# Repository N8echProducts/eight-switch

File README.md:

# eight-switch
Open Source Utf-8 direct keyboard

## Buying
- [n8ech store](https://store.n8ech.com/collections/eight-switch-binary-keyboard)
- [Tindie (KB Edition DIY Kit)](https://www.tindie.com/products/n8ech/eight-switch-kb-edition-diy-kit/)

## Using
ASCII inputs work on more-or-less any device that takes a usb keyboard out of the box.
1. Plug in the eight-switch
1. Select a printable ascii code using the toggle switches
1. Press the button

## UTF-8
Utf-8 inputs are currently supported on the following systems, but some only after enabling unicode direct hex input on the computer.

### MacOS
1. Enable unicode direct input (only needed once)
    1. Open "System Settings"
    2. Open the "Keyboard" menu
    3. Open the "Input Sources" menu
    4. Add "Unicode Hex Input" from the "Others" menu
2. Flip all keys on your eight-switch off
3. Plug in the eight-switch

### Windows
1. Enable Unicode direct input (only needed once)
    1. Press Win + R to open "RUN"
    2. Type regedit and hit Enter to open the Registry Editor.
    3. Navigate to HKEY_CURRENT_USER\Control Panel\Input Method.
    4. Right-click the empty space in the right pane,
    5. select New > String Value, and name it EnableHexNumpad.Double-click EnableHexNumpad,
    6. set the Value data to 1,
    7. click OK.
    8. Restart your computer
1. Flip all keys on your eight-switch off except for the right-most switch (00000001)
2. Plug in the eight-switch

## Firmware Updates
Firmware can be found on the ["Releases" page](https://github.com/N8echProducts/eight-switch/releases) in this repository
### Flashing new updates
the eight-switch is based on the Raspberry pi rp2040 chip, which makes flashing the firmware trivial.
1. Hold down the "flash firmware" button (the button that isn't the push-button to send sequences to the computer) while plugging the device into your computer.
2. drag the .uf2 file from your computer to the drive the device is presenting itself as
3. wait for the device to restart

## QMK mode
The KB editions can be loaded with [QMK](https://qmk.fm)
- Note: The qmk implementation is not the core implementation of the project and is thus vibecoded. Anything in the `qmk-firmware` directory may be considered "slop" but it does seem to work as far as I have tested it. Prebuilt `.uf2` files for a nonsense keymap are attached to releases

## AI disclosure
The product and firmware was all hand-designed/coded with only chatbot style glorified Google Search patterns to/from Claude code.
The utf-8 booklet was nearly entirely vibecoded beyond the initial implementation.
The CI setup was painfully ai assisted and I regret not doing it myself due to the hassle the AI brought
All documentation is written by hand with AI used as glorified Google search.

My general policy: I strive to put out work at the highest quality, with an emphasis on the things people will care about and interact with the most. I allow AI in my workflows only in places where it would not be feasible to do it by hand, and where I can carefully monitor and guage the output to be to my standards.

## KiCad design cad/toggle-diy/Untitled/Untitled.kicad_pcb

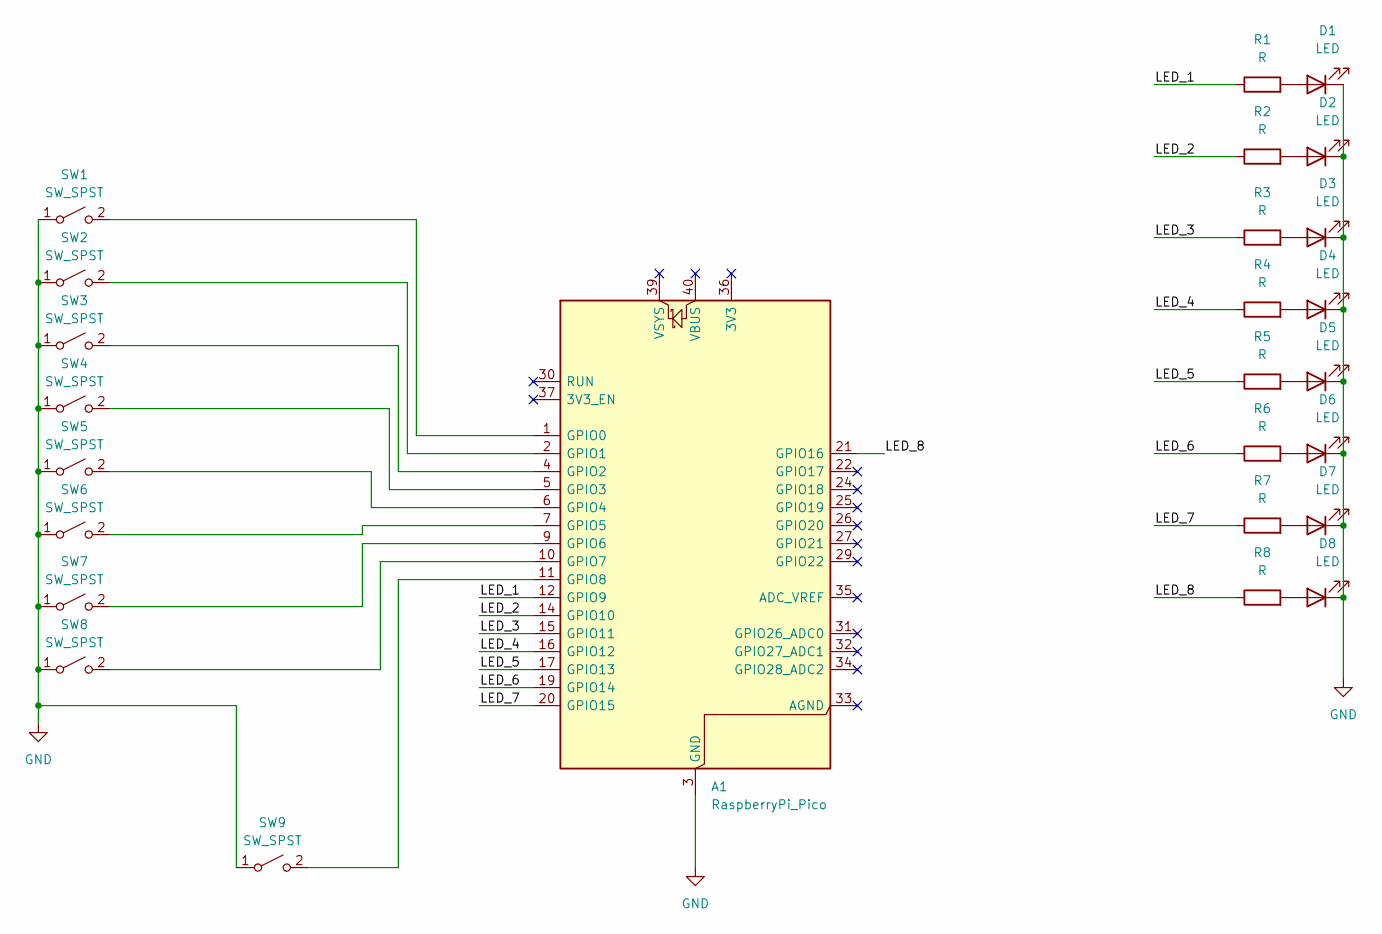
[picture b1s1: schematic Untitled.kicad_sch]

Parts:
A1: RaspberryPi_Pico; RaspberryPi_Pico_Common_SMD
D1, D2, D3, D4, D5, D6, D7, D8: LED; LED_D5.0mm
R1, R2, R3, R4, R5, R6, R7, R8: R; R_Axial_DIN0207_L6.3mm_D2.5mm_P10.16mm_Horizontal
SW1, SW2, SW3, SW4, SW5, SW6, SW7, SW8: SW_SPST; mn11ss1w03_1
SW9: SW_SPST; SW_Cherry_MX_PCB_1.00u

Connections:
/LED_1: A1.12 (GPIO9), R1.1
/LED_2: A1.14 (GPIO10), R2.1
/LED_3: A1.15 (GPIO11), R3.1
/LED_4: A1.16 (GPIO12), R4.1
/LED_5: A1.17 (GPIO13), R5.1
/LED_6: A1.19 (GPIO14), R6.1
/LED_7: A1.20 (GPIO15), R7.1
/LED_8: A1.21 (GPIO16), R8.1
GND: A1.3 (GND), A1.8 (GND), A1.13 (GND), A1.18 (GND), A1.23 (GND), A1.28 (GND), A1.38 (GND), D1.1 (K), D2.1 (K), D3.1 (K), D4.1 (K), D5.1 (K), D6.1 (K), D7.1 (K), D8.1 (K), SW1.1 (A), SW2.1 (A), SW3.1 (A), SW4.1 (A), SW5.1 (A), SW6.1 (A), SW7.1 (A), SW8.1 (A), SW9.1 (A)
unnamed: A1.1 (GPIO0), SW1.2 (B)
unnamed: A1.2 (GPIO1), SW2.2 (B)
unnamed: A1.4 (GPIO2), SW3.2 (B)
unnamed: A1.5 (GPIO3), SW4.2 (B)
unnamed: A1.6 (GPIO4), SW5.2 (B)
unnamed: A1.7 (GPIO5), SW6.2 (B)
unnamed: A1.9 (GPIO6), SW7.2 (B)
unnamed: A1.10 (GPIO7), SW8.2 (B)
unnamed: A1.11 (GPIO8), SW9.2 (B)
unnamed: D1.2 (A), R1.2
unnamed: D2.2 (A), R2.2
unnamed: D3.2 (A), R3.2
unnamed: D4.2 (A), R4.2
unnamed: D5.2 (A), R5.2
unnamed: D6.2 (A), R6.2
unnamed: D7.2 (A), R7.2
unnamed: D8.2 (A), R8.2

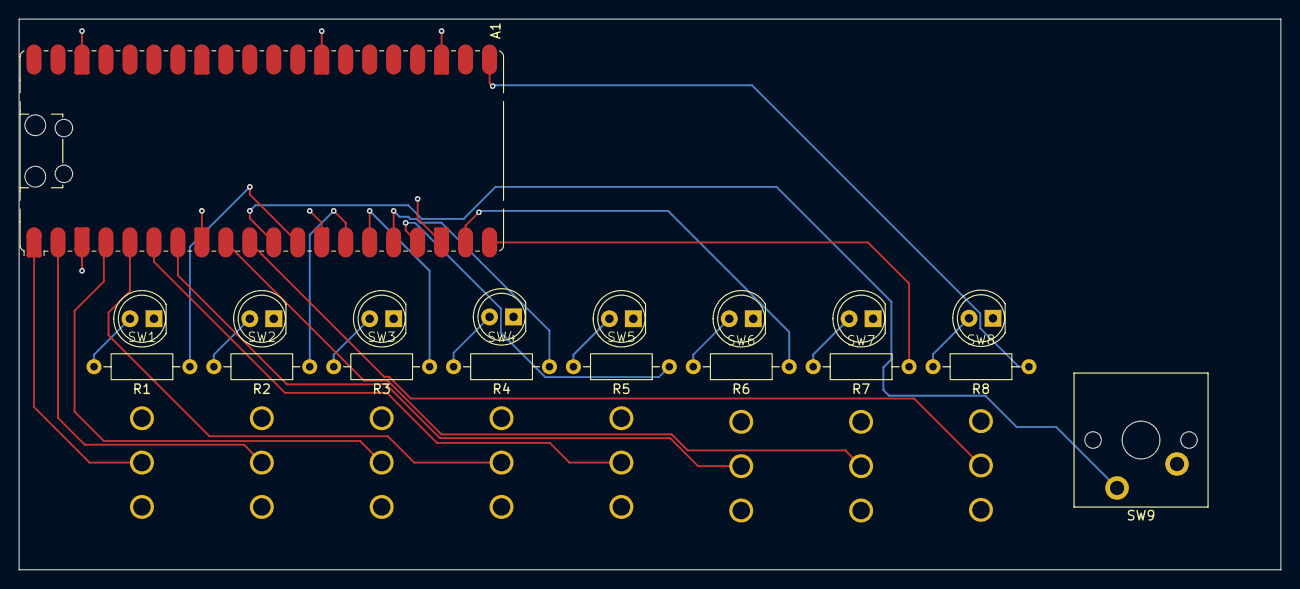
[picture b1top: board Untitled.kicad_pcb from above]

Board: 4 copper layers, 133.7 x 58.3 mm, 26 parts (0 on the bottom side), 26 nets.

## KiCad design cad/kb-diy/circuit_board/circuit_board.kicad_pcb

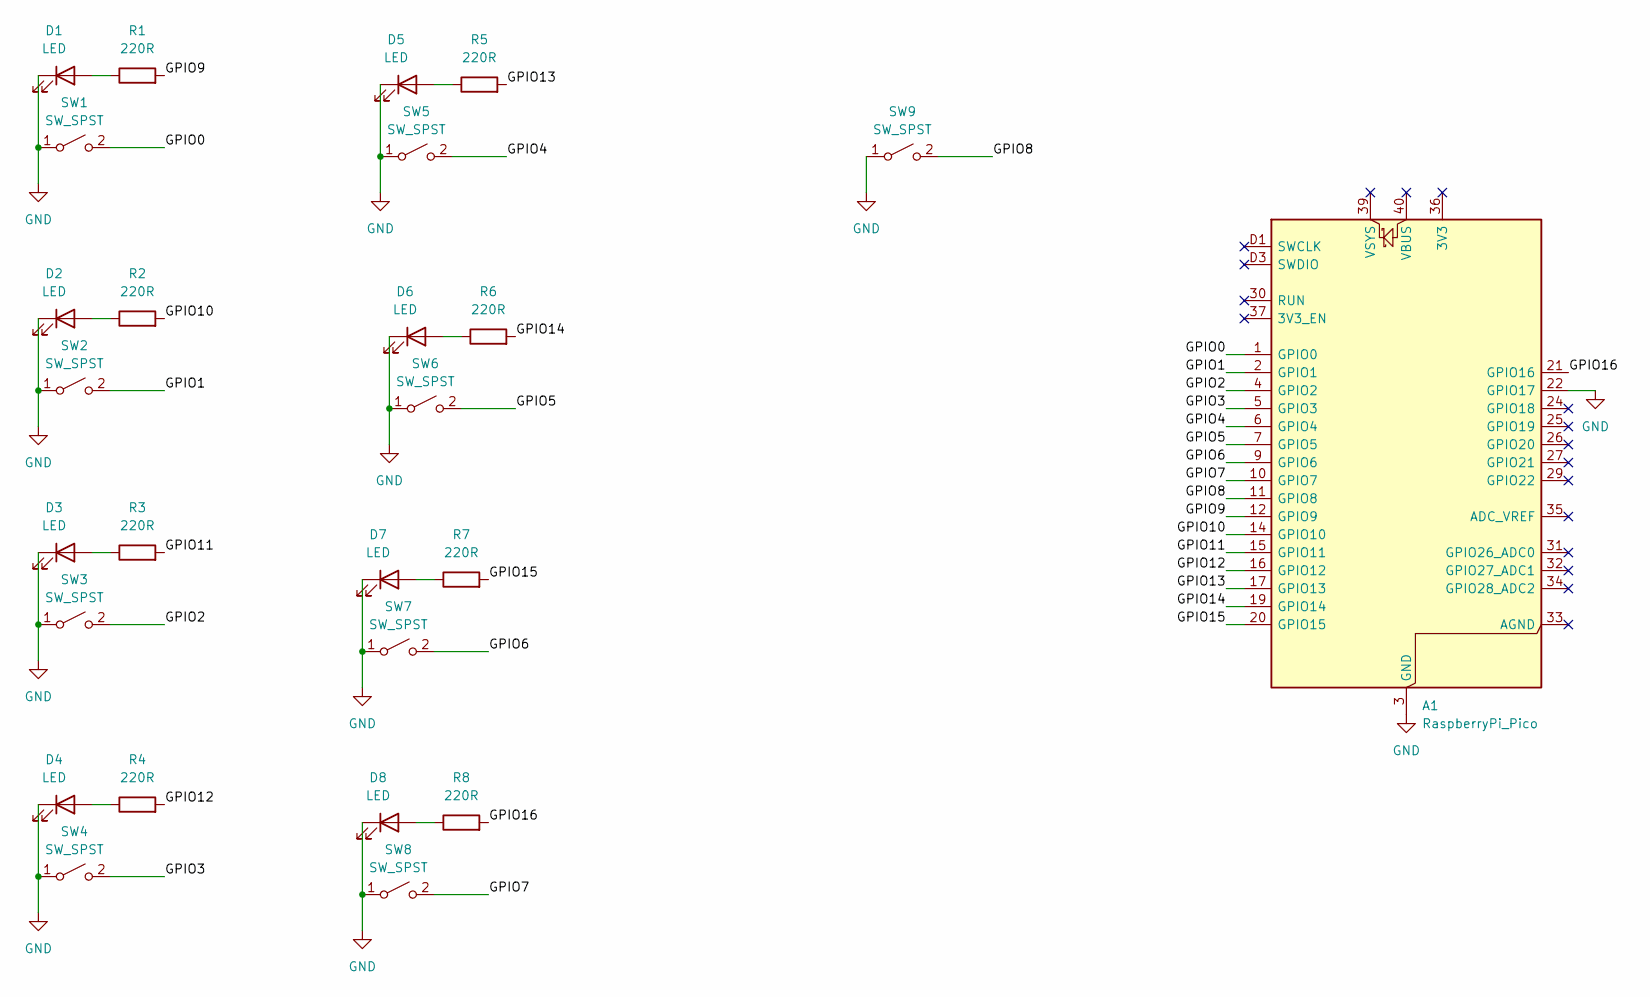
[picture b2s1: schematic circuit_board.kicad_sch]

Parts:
A1: RaspberryPi_Pico; RaspberryPi_Pico_SMD_HandSolder
D1, D2, D3, D4, D5, D6, D7, D8: LED; LED_D1.8mm_W3.3mm_H2.4mm
R1, R2, R3, R4, R5, R6, R7, R8: 220R; R_Axial_DIN0204_L3.6mm_D1.6mm_P5.08mm_Horizontal
SW1, SW2, SW3, SW4, SW5, SW6, SW7, SW8: SW_SPST; SW_Cherry_MX_PCB_1.00u
SW9: SW_SPST; SW_Cherry_MX_PCB_2.25u

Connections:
/GPIO0: A1.1 (GPIO0), SW1.2 (B)
/GPIO1: A1.2 (GPIO1), SW2.2 (B)
/GPIO2: A1.4 (GPIO2), SW3.2 (B)
/GPIO3: A1.5 (GPIO3), SW4.2 (B)
/GPIO4: A1.6 (GPIO4), SW5.2 (B)
/GPIO5: A1.7 (GPIO5), SW6.2 (B)
/GPIO6: A1.9 (GPIO6), SW7.2 (B)
/GPIO7: A1.10 (GPIO7), SW8.2 (B)
/GPIO8: A1.11 (GPIO8), SW9.2 (B)
/GPIO9: A1.12 (GPIO9), R1.2
/GPIO10: A1.14 (GPIO10), R2.2
/GPIO11: A1.15 (GPIO11), R3.2
/GPIO12: A1.16 (GPIO12), R4.2
/GPIO13: A1.17 (GPIO13), R5.2
/GPIO14: A1.19 (GPIO14), R6.2
/GPIO15: A1.20 (GPIO15), R7.2
/GPIO16: A1.21 (GPIO16), R8.2
GND: A1.3 (GND), A1.8 (GND), A1.13 (GND), A1.18 (GND), A1.22 (GPIO17), A1.23 (GND), A1.28 (GND), A1.38 (GND), A1.D2 (GND), D1.1 (K), D2.1 (K), D3.1 (K), D4.1 (K), D5.1 (K), D6.1 (K), D7.1 (K), D8.1 (K), SW1.1 (A), SW2.1 (A), SW3.1 (A), SW4.1 (A), SW5.1 (A), SW6.1 (A), SW7.1 (A), SW8.1 (A), SW9.1 (A)
unnamed: D1.2 (A), R1.1
unnamed: D2.2 (A), R2.1
unnamed: D3.2 (A), R3.1
unnamed: D4.2 (A), R4.1
unnamed: D5.2 (A), R5.1
unnamed: D6.2 (A), R6.1
unnamed: D7.2 (A), R7.1
unnamed: D8.2 (A), R8.1

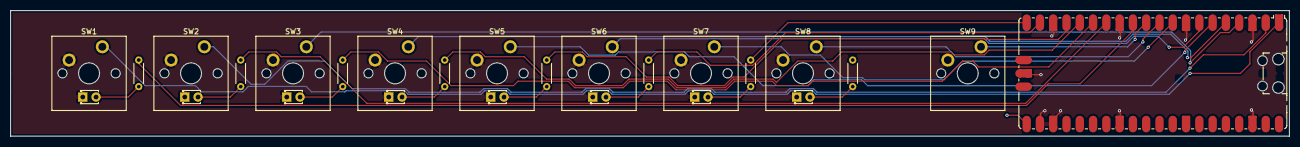
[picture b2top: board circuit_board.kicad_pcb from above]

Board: 4 copper layers, 244.5 x 24.0 mm, 26 parts (0 on the bottom side), 26 nets.

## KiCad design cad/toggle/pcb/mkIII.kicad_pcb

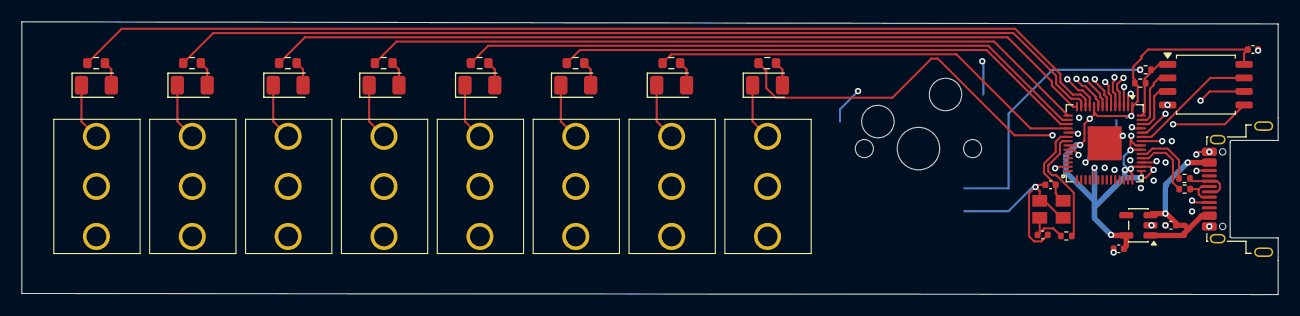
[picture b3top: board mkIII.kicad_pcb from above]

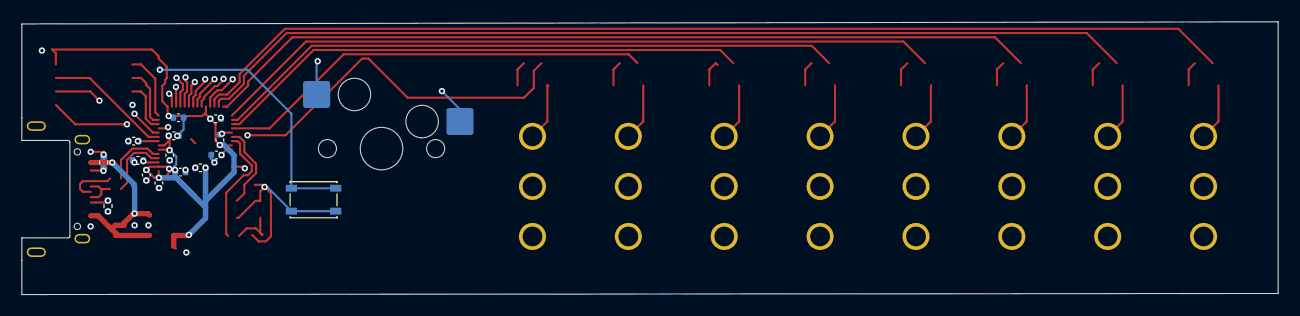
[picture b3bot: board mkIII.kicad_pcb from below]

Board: 4 copper layers, 117.9 x 25.6 mm, 55 parts (16 on the bottom side), 45 nets.

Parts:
C1, C2, C3, C4, C5, C6, C8, C9, C11, C12, C13: 100n; C_0402_1005Metric
C7, C10: 1u; C_0402_1005Metric
C14, C15: 15p; C_0402_1005Metric
C16, C17: 10u; C_0402_1005Metric
D1, D2, D3, D4, D5, D6, D7, D8: LED; LED_1206_3216Metric
J1: USB_C_Receptacle_USB2.0_16P; USB_C_Receptacle_Amphenol_12401948E412A
R1, R2: 5.1k; R_0402_1005Metric
R3, R4: 27; R_0402_1005Metric
R5, R7: 1k; R_0402_1005Metric
R6: 10k; R_0402_1005Metric
R8, R9, R10, R11, R12, R13, R14, R15: R; R_0603_1608Metric
SW1: SW_Push; SW_SPST_PTS810
SW2, SW3, SW4, SW5, SW6, SW7, SW8, SW9: SW_SPST; mn11ss1w03_1
SW10: SW_SPST; MX100H
U1: RP2040; QFN-56-1EP_7x7mm_P0.4mm_EP3.2x3.2mm
U2: W25Q16JVSS; SOIC-8_5.3x5.3mm_P1.27mm
U3: XC6220B331MR; SOT-23-5
Y1: Crystal_GND24; ABM8-272-T3_ABR

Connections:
+1V1: C10.2, C11.1, C12.1, U1.23 (DVDD), U1.45 (VREG_VOUT), U1.50 (DVDD)
+3.3V: C1.1, C2.1, C3.1, C4.1, C5.1, C6.1, C7.1, C8.2, C9.2, C13.1, C17.1, R6.1, U1.1 (IOVDD), U1.10 (IOVDD), U1.22 (IOVDD), U1.33 (IOVDD), U1.42 (IOVDD), U1.43 (ADC_AVDD), U1.44 (VREG_VIN), U1.48 (USB_VDD), U1.49 (IOVDD), U2.8 (VCC), U3.5 (VOUT)
/rp/QSPI_SCLK: U1.52 (QSPI_SCLK), U2.6 (CLK)
/rp/QSPI_SD0: U1.53 (QSPI_SD0), U2.5 (DI/IO_{0})
/rp/QSPI_SD1: U1.55 (QSPI_SD1), U2.2 (DO/IO_{1})
/rp/QSPI_SD2: U1.54 (QSPI_SD2), U2.3 (~WP/IO_{2})
/rp/QSPI_SD3: U1.51 (QSPI_SD3), U2.7 (~HOLD/~RESET/IO_{3})
/rp/XIN: C15.1, U1.20 (XIN), Y1.1
/rp/XOUT: R7.2, U1.21 (XOUT)
/rp/usb_dM: R3.2, U1.46 (USB_DM)
/rp/usb_dP: R4.2, U1.47 (USB_DP)
/rp/~QSPI_SS: R5.2, R6.2, U1.56 (~QSPI_SS), U2.1 (~CS)
GND: C1.2, C2.2, C3.2, C4.2, C5.2, C6.2, C7.2, C8.1, C9.1, C10.1, C11.2, C12.2, C13.2, C14.2, C15.2, C16.2, C17.2, D1.1 (K), D2.1 (K), D3.1 (K), D4.1 (K), D5.1 (K), D6.1 (K), D7.1 (K), D8.1 (K), J1.A1 (GND), J1.A12 (GND), J1.B1 (GND), J1.B12 (GND), J1.SH (SHIELD), R1.2, R2.2, SW1.1, SW2.1 (A), SW3.1 (A), SW4.1 (A), SW5.1 (A), SW6.1 (A), SW7.1 (A), SW8.1 (A), SW9.1 (A), SW10.1 (A), U1.19 (TESTEN), U1.57 (GND), U2.4 (GND), U3.2 (GND), Y1.2 (G), Y1.4 (G)
GPIO0: SW2.2 (B), U1.2 (GPIO0)
GPIO1: SW3.2 (B), U1.3 (GPIO1)
GPIO2: SW4.2 (B), U1.4 (GPIO2)
GPIO3: SW5.2 (B), U1.5 (GPIO3)
GPIO4: SW6.2 (B), U1.6 (GPIO4)
GPIO5: SW7.2 (B), U1.7 (GPIO5)
GPIO6: SW8.2 (B), U1.8 (GPIO6)
GPIO7: SW9.2 (B), U1.9 (GPIO7)
GPIO8: SW10.2 (B), U1.11 (GPIO8)
GPIO9: R8.2, U1.12 (GPIO9)
GPIO10: R9.2, U1.13 (GPIO10)
GPIO11: R10.2, U1.14 (GPIO11)
GPIO12: R11.2, U1.15 (GPIO12)
GPIO13: R12.2, U1.16 (GPIO13)
GPIO14: R13.2, U1.17 (GPIO14)
GPIO15: R14.2, U1.18 (GPIO15)
GPIO16: R15.2, U1.27 (GPIO16)
unnamed: C14.1, R7.1, Y1.3
unnamed: D1.2 (A), R8.1
unnamed: D2.2 (A), R9.1
unnamed: D3.2 (A), R10.1
unnamed: D4.2 (A), R11.1
unnamed: D5.2 (A), R12.1
unnamed: D6.2 (A), R13.1
unnamed: D7.2 (A), R14.1
unnamed: D8.2 (A), R15.1
unnamed: J1.A5 (CC1), R1.1
unnamed: J1.B5 (CC2), R2.1
unnamed: J1.A6 (D+), J1.B6 (D+), R4.1
unnamed: J1.A7 (D-), J1.B7 (D-), R3.1
unnamed: R5.1, SW1.2
VBUS: C16.1, J1.A4 (VBUS), J1.A9 (VBUS), J1.B4 (VBUS), J1.B9 (VBUS), U3.1 (VIN), U3.3 (CE)

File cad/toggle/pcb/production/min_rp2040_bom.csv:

Designator,Footprint,Quantity,Value,LCSC Part #
"C1, C11, C12, C13, C2, C3, C4, C5, C6, C8, C9",0402,11,100n,
"C10, C7",0402,2,1u,
"C14, C15",0402,2,15p,
"C16, C17",0402,2,10u,
J1,USB_C_Receptacle_Amphenol_12401948E412A,1,USB_C_Receptacle_USB2.0_16P,
"R1, R2",0402,2,5.1k,
"R3, R4",0402,2,27,
"R5, R7",0402,2,1k,
R6,0402,1,10k,
SW1,SW_SPST_PTS810,1,SW_Push,
U1,QFN-56-1EP_7x7mm_P0.4mm_EP3.2x3.2mm,1,RP2040,
U2,SOIC-8_5.3x5.3mm_P1.27mm,1,W25Q16JVSS,
U3,SOT-23-5,1,XC6220B331MR,
Y1,ABM8-272-T3_ABR,1,Crystal_GND24,

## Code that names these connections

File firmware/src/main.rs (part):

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        USB_DEVICE = Some(usb_dev);
    }

    let mut switch_or_keys_pin = pins.gpio17.into_pull_up_input();

    let mut keys: AnySwitchBoard = match switch_or_keys_pin.is_low().unwrap() {
        // switch edition
        false => {
            let switches = [
                pins.gpio7.into_pull_up_input().into_dyn_pin(),
                pins.gpio6.into_pull_up_input().into_dyn_pin(),
                pins.gpio5.into_pull_up_input().into_dyn_pin(),
                pins.gpio4.into_pull_up_input().into_dyn_pin(),
                pins.gpio3.into_pull_up_input().into_dyn_pin(),
                pins.gpio2.into_pull_up_input().into_dyn_pin(),
                pins.gpio1.into_pull_up_input().into_dyn_pin(),
                pins.gpio0.into_pull_up_input().into_dyn_pin(),
            ];
            AnySwitchBoard::Toggle(ToggleBoard::new(switches))
        }
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        true => {
            // set up input pins
            let keyswitches = [
                DebouncedButton::new(pins.gpio7.into_pull_up_input().into_dyn_pin()),
                DebouncedButton::new(pins.gpio6.into_pull_up_input().into_dyn_pin()),
                DebouncedButton::new(pins.gpio5.into_pull_up_input().into_dyn_pin()),
                DebouncedButton::new(pins.gpio4.into_pull_up_input().into_dyn_pin()),
                DebouncedButton::new(pins.gpio3.into_pull_up_input().into_dyn_pin()),
                DebouncedButton::new(pins.gpio2.into_pull_up_input().into_dyn_pin()),
                DebouncedButton::new(pins.gpio1.into_pull_up_input().into_dyn_pin()),
                DebouncedButton::new(pins.gpio0.into_pull_up_input().into_dyn_pin()),
            ];

            let mut keys = CherryBoard {
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
    // pwm for gpio 9
    let led1 = &mut pwm4.channel_b;
    led1.output_to(pins.gpio9);
    led1.set_duty_cycle_percent(0);
    // pwm for gpio 10
    let led2 = &mut pwm5.channel_a;
    led2.output_to(pins.gpio10);
    led2.set_duty_cycle_percent(0);
    // pwm for gpio 11
    let led3 = &mut pwm5.channel_b;
    led3.output_to(pins.gpio11);
    led3.set_duty_cycle_percent(0);
    // pwm for gpio 12
    let led4 = &mut pwm6.channel_a;
    led4.output_to(pins.gpio12);
    led4.set_duty_cycle_percent(0);
    // pwm for gpio 13
    let led5 = &mut pwm6.channel_b;
    led5.output_to(pins.gpio13);
    led5.set_duty_cycle_percent(0);
    // pwm for gpio 14
    let led6 = &mut pwm7.channel_a;
    led6.output_to(pins.gpio14);
    led6.set_duty_cycle_percent(0);
    // pwm for gpio 15
    let led7 = &mut pwm7.channel_b;
    led7.output_to(pins.gpio15);
    led7.set_duty_cycle_percent(0);
    // pwm for gpio 16
    let led8 = &mut pwm0.channel_a;
    led8.output_to(pins.gpio16);
    led8.set_duty_cycle_percent(0);

    let mut lights: [&mut dyn SetDutyCycle<Error = core::convert::Infallible>; 8] =
        [led8, led7, led6, led5, led4, led3, led2, led1];
    let button = pins.gpio8.into_pull_up_input().into_dyn_pin();

    let os = match keys.get_state_raw() {
        1 => OsInputMode::Win,
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
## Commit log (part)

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2026-06-21 remove all history to make stuff clean
